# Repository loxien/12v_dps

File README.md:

<h1 align="center">PΦW12</h1>

<p align="center">A 12V Dual Power Supply for Small Eurorack Systems powered by USB-C.</p>

# Documentation
Still work in progress ...

# License
This project is made available under a CC-BY-NC-SA-3.0 license.

If you want to make a PCB for your own use, go ahead. Please do not make and sell these in bulk.

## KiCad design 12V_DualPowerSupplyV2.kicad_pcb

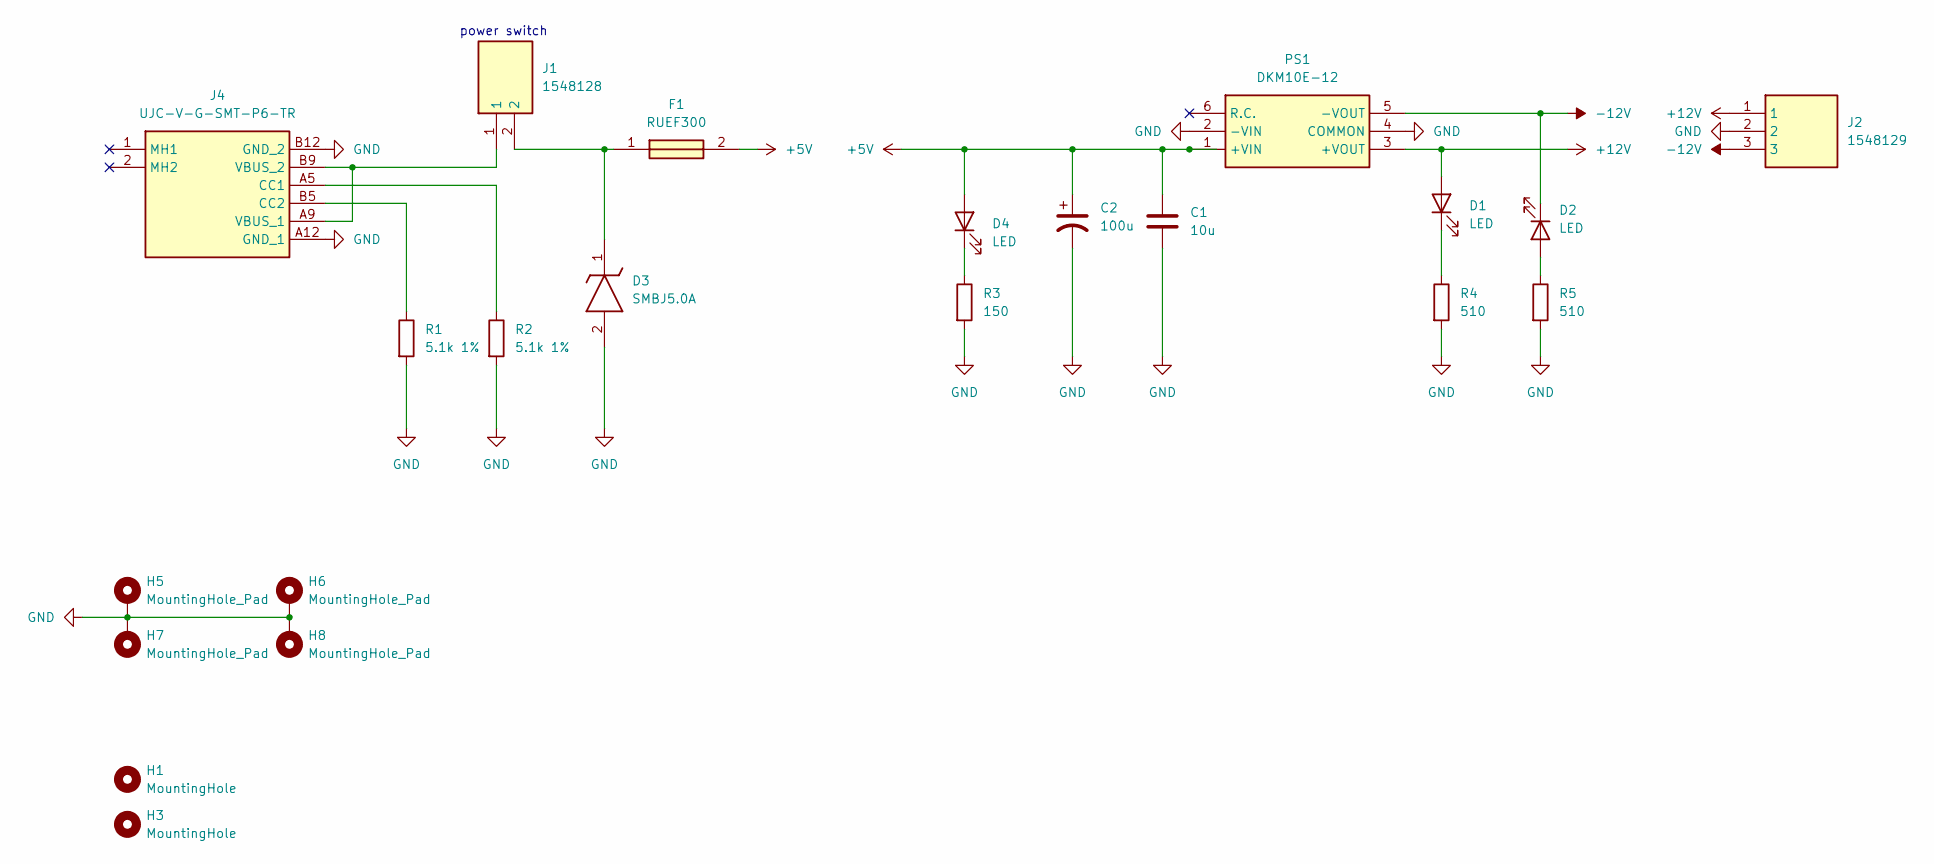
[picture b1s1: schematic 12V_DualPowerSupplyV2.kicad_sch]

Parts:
C1: 10u; C_Radial_D5.0mm_H11.0mm_P2.00mm
C2: 100u; C_Radial_D6.3mm_H7.0mm_P2.50mm
D1, D2, D4: LED; LED_D5.0mm
D3: SMBJ5.0A; Mouser Part Number 576-SMBJ5.0A
F1: RUEF300; Mouser Part Number 650-RUEF300
H1, H3: MountingHole; MountingHole_3.2mm_M3
H5, H6, H7, H8: MountingHole_Pad; MountingHole_2.2mm_M2_DIN965_Pad
J1: 1548128; Mouser Part Number 651-1548128
J2: 1548129; Mouser Part Number 651-1548129
J4: UJC-V-G-SMT-P6-TR; UJCVGSMTP6TR; Mouser Part Number 179-UJCVGSMTP6TR
PS1: DKM10E-12; DKM10E12; Mouser Part Number 709-DKM10E-12
R1, R2: 5.1k 1%; R_Axial_DIN0207_L6.3mm_D2.5mm_P7.62mm_Horizontal
R3: 150; R_Axial_DIN0207_L6.3mm_D2.5mm_P7.62mm_Horizontal
R4, R5: 510; R_Axial_DIN0207_L6.3mm_D2.5mm_P7.62mm_Horizontal

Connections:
+5V: C1.1, C2.1, D4.2 (A), F1.2, PS1.1 (+VIN)
+12V: D1.2 (A), J2.1, PS1.3 (+VOUT)
-12V: D2.1 (K), J2.3, PS1.5 (-VOUT)
GND: C1.2, C2.2, D3.2 (A), H5.1, H6.1, H7.1, H8.1, J2.2, J4.A12 (GND_1), J4.B12 (GND_2), PS1.2 (-VIN), PS1.4 (COMMON), R1.2, R2.2, R3.2, R4.2, R5.2
unnamed: D1.1 (K), R4.1
unnamed: D2.2 (A), R5.1
unnamed: D3.1 (K), F1.1, J1.2
unnamed: D4.1 (K), R3.1
unnamed: J4.A5 (CC1), R2.1
unnamed: J4.B5 (CC2), R1.1
unnamed: J1.1, J4.A9 (VBUS_1), J4.B9 (VBUS_2)

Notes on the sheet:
power switch

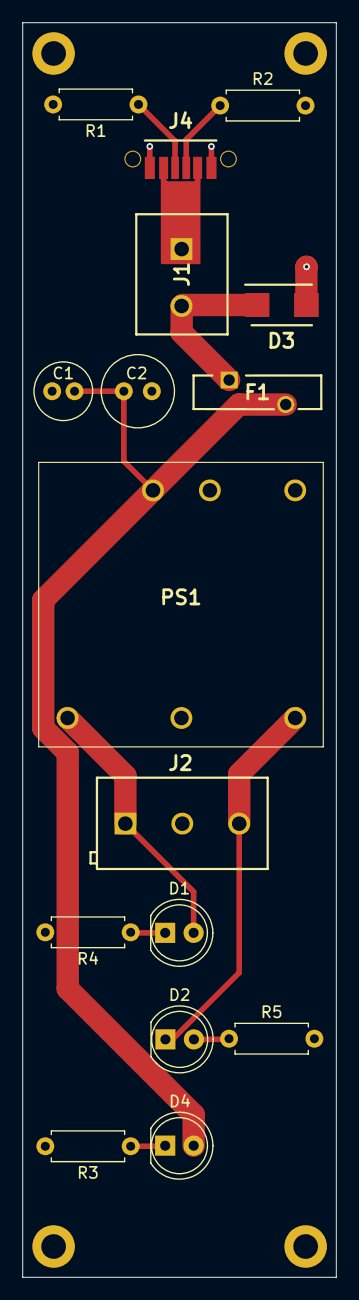
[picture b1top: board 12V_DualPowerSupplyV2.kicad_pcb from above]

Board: 2 copper layers, 28.0 x 112.0 mm, 20 parts (0 on the bottom side), 11 nets.

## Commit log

2025-09-23 Create test
2025-09-23 Rename 12V_DualPowerSupplyV2.kicad_pcb to KiCad_files/12V_DualPowerSupplyV2.kicad_pcb
2025-09-23 Rename 12V_DualPowerSupplyV2.kicad_pro to KiCad_files/12V_DualPowerSupplyV2.kicad_pro
2025-09-23 Rename 12V_DualPowerSupplyV2.kicad_sch to KiCad_files/12V_DualPowerSupplyV2.kicad_sch
2025-09-29 Rename logo.png to misc/logo.png
